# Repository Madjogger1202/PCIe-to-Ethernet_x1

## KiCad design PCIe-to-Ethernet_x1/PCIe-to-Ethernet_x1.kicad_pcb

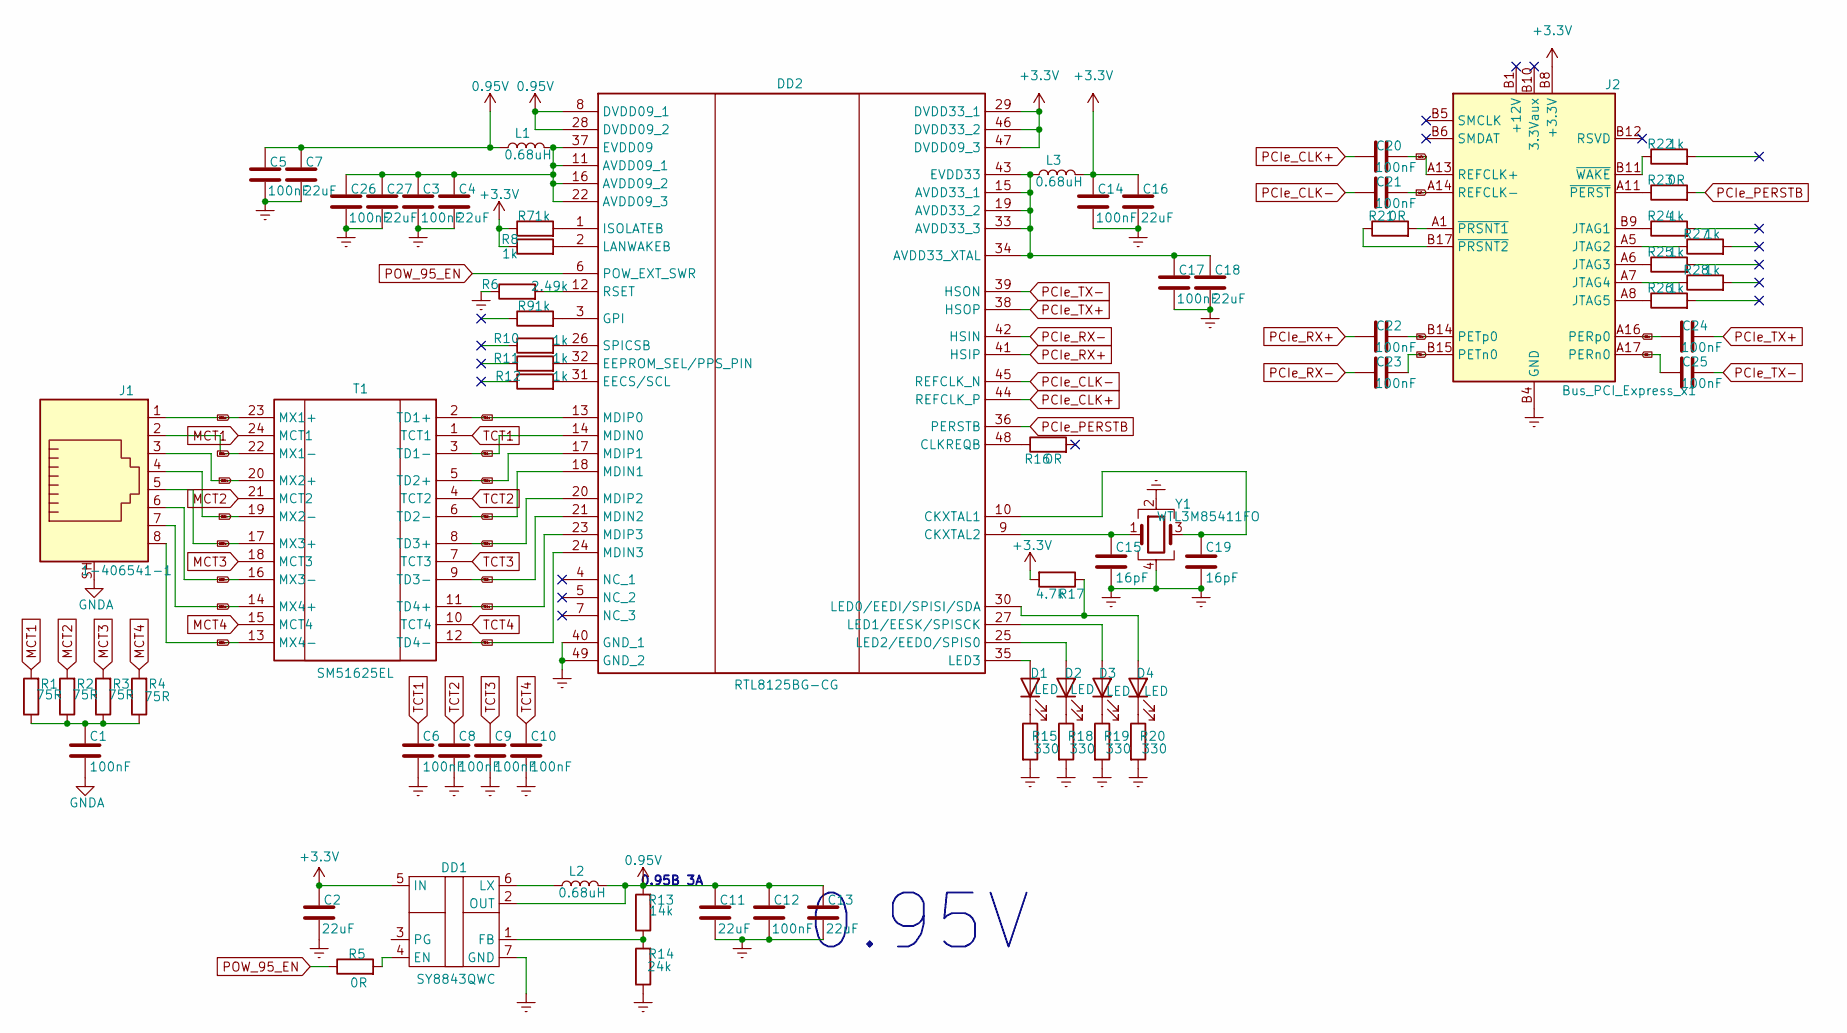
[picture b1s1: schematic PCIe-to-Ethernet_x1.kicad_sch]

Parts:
C1, C3, C5, C6, C8, C9, C10, C12, C14, C17, C20, C21, C22, C23, C24, C25, C26: 100nF; C_0402_1005Metric
C2, C4, C7, C11, C13, C16, C18, C27: 22uF; C_0402_1005Metric
C15, C19: 16pF; C_0402_1005Metric
D1, D2, D3, D4: LED; LED_0402_1005Metric
DD1: SY8843QWC
DD2: RTL8125BG-CG; QFN40P600X600X100-49N; Manufacturer_Part_Number RTL8125BG-CG
J1: 1-406541-1; RJ45_Amphenol_RJHSE5380
J2: Bus_PCI_Express_x1; BUS_PCIexpress_x1
L1, L2, L3: 0.68uH; L_Cenker_CKCS4020
R1, R2, R3, R4: 75R; R_0402_1005Metric
R5, R16, R21, R23: 0R; R_0402_1005Metric
R6: 2.49k; R_0402_1005Metric
R7, R8, R9, R10, R11, R12, R22, R24, R25, R26, R27, R28: 1k; R_0402_1005Metric
R13: 14k; R_0402_1005Metric
R14: 24k; R_0402_1005Metric
R15, R18, R19, R20: 330; R_0402_1005Metric
R17: 4.7k; R_0402_1005Metric
T1: SM51625EL; SOIC127P1600X625-24N; Manufacturer_Part_Number SM51625EL; Mouser Part Number 652-SM51625EL
Y1: WTL3M85411FO; Crystal_SMD_3225-4Pin_3.2x2.5mm

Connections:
0.95V: C5.1, C7.1, C11.1, C12.1, C13.1, DD1.2 (OUT), DD2.8 (DVDD09_1), DD2.28 (DVDD09_2), L1.1, L2.2, R13.2
+3.3V: C2.1, C14.1, C16.1, DD1.5 (IN), DD2.29 (DVDD33_1), DD2.46 (DVDD33_2), DD2.47 (DVDD09_3), J2.A9 (+3.3V), J2.A10 (+3.3V), J2.B8 (+3.3V), L3.2, R7.1, R8.1, R17.2
Earth: C2.2, C3.2, C4.2, C5.2, C6.2, C7.2, C8.2, C9.2, C10.2, C11.2, C12.2, C13.2, C14.2, C15.2, C16.2, C17.2, C18.2, C19.2, C26.2, C27.2, DD1.7 (GND), DD2.40 (GND_1), DD2.49 (GND_2), J2.A4 (GND), J2.A12 (GND), J2.A15 (GND), J2.A18 (GND), J2.B4 (GND), J2.B7 (GND), J2.B13 (GND), J2.B16 (GND), J2.B18 (GND), R6.1, R14.1, R15.2, R18.2, R19.2, R20.2, Y1.2, Y1.4
GNDA: C1.2, J1.SH
MCT1: R1.2, T1.24 (MCT1)
MCT2: R2.2, T1.21 (MCT2)
MCT3: R3.2, T1.18 (MCT3)
MCT4: R4.2, T1.15 (MCT4)
MX1+: J1.1, T1.23 (MX1+)
MX1-: J1.2, T1.22 (MX1-)
MX2+: J1.3, T1.20 (MX2+)
MX2-: J1.4, T1.19 (MX2-)
MX3+: J1.5, T1.17 (MX3+)
MX3-: J1.6, T1.16 (MX3-)
MX4+: J1.7, T1.14 (MX4+)
MX4-: J1.8, T1.13 (MX4-)
unnamed: C1.1, R1.1, R2.1, R3.1, R4.1
unnamed: D1.2 (A), DD2.35 (LED3)
unnamed: D1.1 (K), R15.1
unnamed: D2.2 (A), DD2.25 (LED2/EEDO/SPIS0)
unnamed: D2.1 (K), R18.1
unnamed: D3.2 (A), DD2.27 (LED1/EESK/SPISCK)
unnamed: D3.1 (K), R19.1
unnamed: D4.2 (A), DD2.30 (LED0/EEDI/SPISI/SDA), R17.1
unnamed: D4.1 (K), R20.1
unnamed: DD1.4 (EN), R5.2
unnamed: DD1.1 (FB), R13.1, R14.2
unnamed: DD1.6 (LX), L2.1
unnamed: C3.1, C4.1, C26.1, C27.1, DD2.11 (AVDD09_1), DD2.16 (AVDD09_2), DD2.22 (AVDD09_3), DD2.37 (EVDD09), L1.2
unnamed: C17.1, C18.1, DD2.15 (AVDD33_1), DD2.19 (AVDD33_2), DD2.33 (AVDD33_3), DD2.34 (AVDD33_XTAL), DD2.43 (EVDD33), L3.1
unnamed: C19.1, DD2.10 (CKXTAL1), Y1.3
unnamed: C15.1, DD2.9 (CKXTAL2), Y1.1
unnamed: DD2.48 (CLKREQB), R16.1
unnamed: DD2.31 (EECS/SCL), R12.2
unnamed: DD2.32 (EEPROM_SEL/PPS_PIN), R11.2
unnamed: DD2.3 (GPI), R9.2
unnamed: DD2.1 (ISOLATEB), R7.2
unnamed: DD2.2 (LANWAKEB), R8.2
unnamed: DD2.12 (RSET), R6.2
unnamed: DD2.26 (SPICSB), R10.2
unnamed: J2.B9 (JTAG1), R24.1
unnamed: J2.A5 (JTAG2), R27.1
unnamed: J2.A6 (JTAG3), R25.1
unnamed: J2.A7 (JTAG4), R28.1
unnamed: J2.A8 (JTAG5), R26.1
unnamed: J2.A11 (~PERST), R23.1
unnamed: J2.A1 (~PRSNT1), R21.2
unnamed: J2.B17 (~PRSNT2), R21.1
unnamed: J2.B11 (~WAKE), R22.1
PCIe_CLK+: C20.1, DD2.44 (REFCLK_P)
PCIe_CLK-: C21.1, DD2.45 (REFCLK_N)
PCIe_PERSTB: DD2.36 (PERSTB), R23.2
PCIe_RX+: C22.1, DD2.41 (HSIP)
PCIe_RX-: C23.1, DD2.42 (HSIN)
PCIe_TX+: C24.2, DD2.38 (HSOP)
PCIe_TX-: C25.2, DD2.39 (HSON)
POW_95_EN: DD2.6 (POW_EXT_SWR), R5.1
RX+: C24.1, J2.A16 (PERp0)
RX-: C25.1, J2.A17 (PERn0)
TCT1: C6.1, T1.1 (TCT1)
TCT2: C8.1, T1.4 (TCT2)
TCT3: C9.1, T1.7 (TCT3)
TCT4: C10.1, T1.10 (TCT4)
TD1+: DD2.13 (MDIP0), T1.2 (TD1+)
TD1-: DD2.14 (MDIN0), T1.3 (TD1-)
TD2+: DD2.17 (MDIP1), T1.5 (TD2+)
TD2-: DD2.18 (MDIN1), T1.6 (TD2-)
TD3+: DD2.20 (MDIP2), T1.8 (TD3+)
TD3-: DD2.21 (MDIN2), T1.9 (TD3-)
TD4+: DD2.23 (MDIP3), T1.11 (TD4+)
TD4-: DD2.24 (MDIN3), T1.12 (TD4-)
TX+: C22.2, J2.B14 (PETp0)
TX-: C23.2, J2.B15 (PETn0)
ref+: C20.2, J2.A13 (REFCLK+)
ref-: C21.2, J2.A14 (REFCLK-)

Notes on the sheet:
0.95В 3А
0.95V

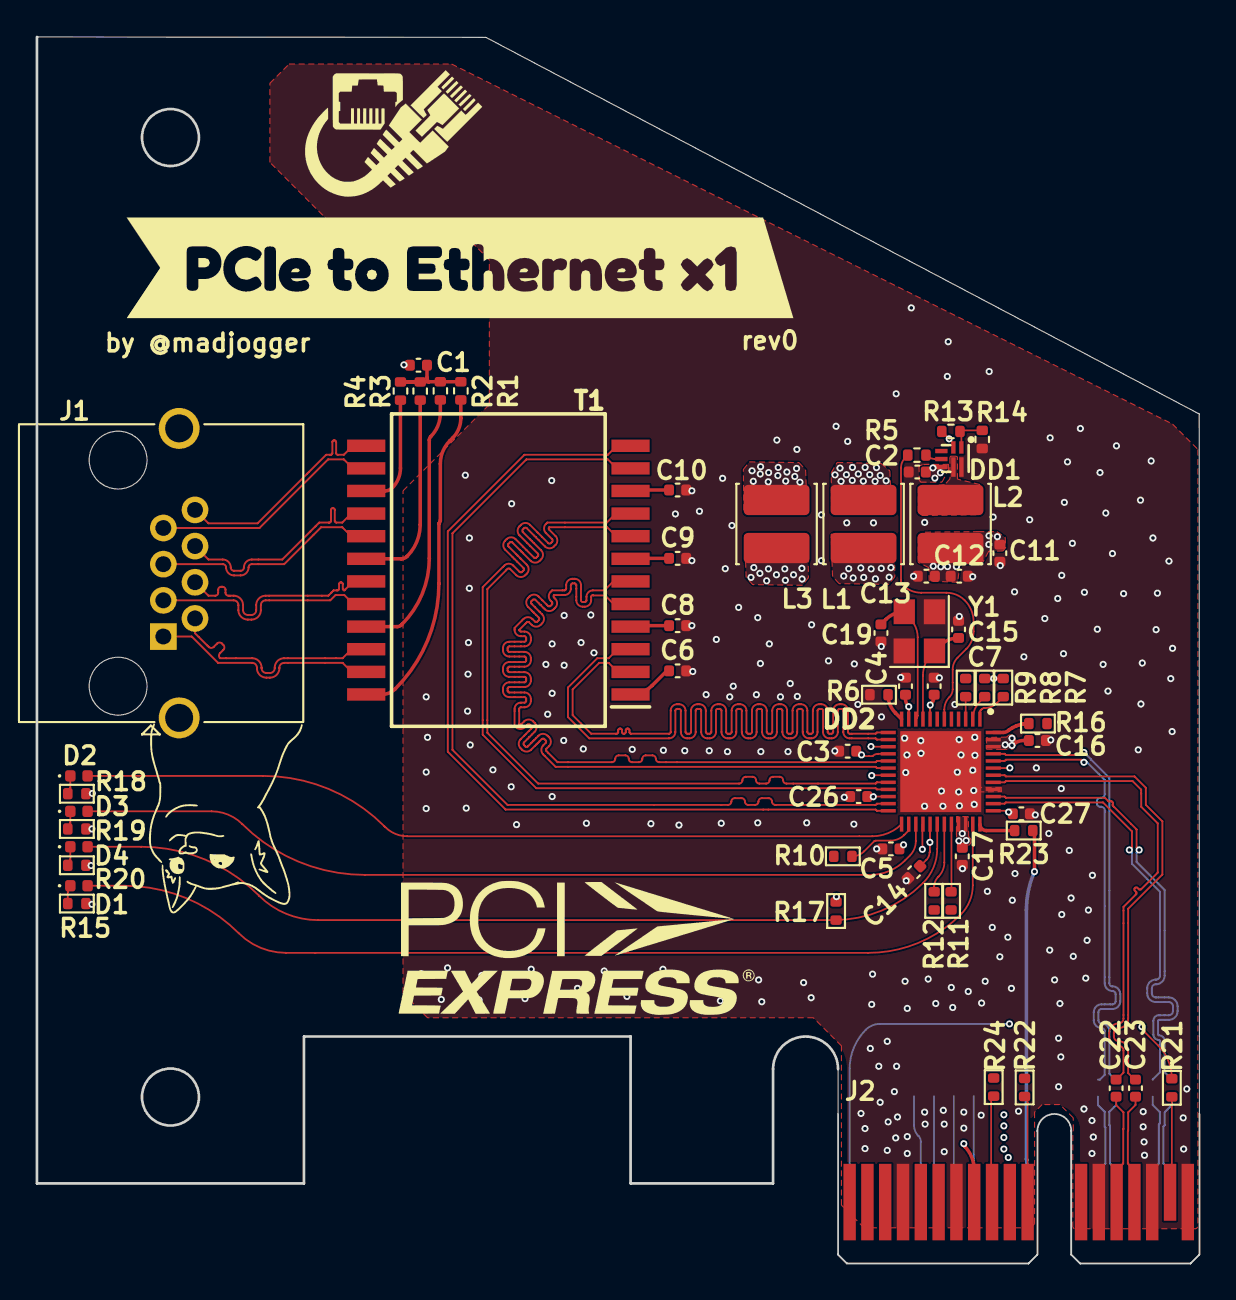
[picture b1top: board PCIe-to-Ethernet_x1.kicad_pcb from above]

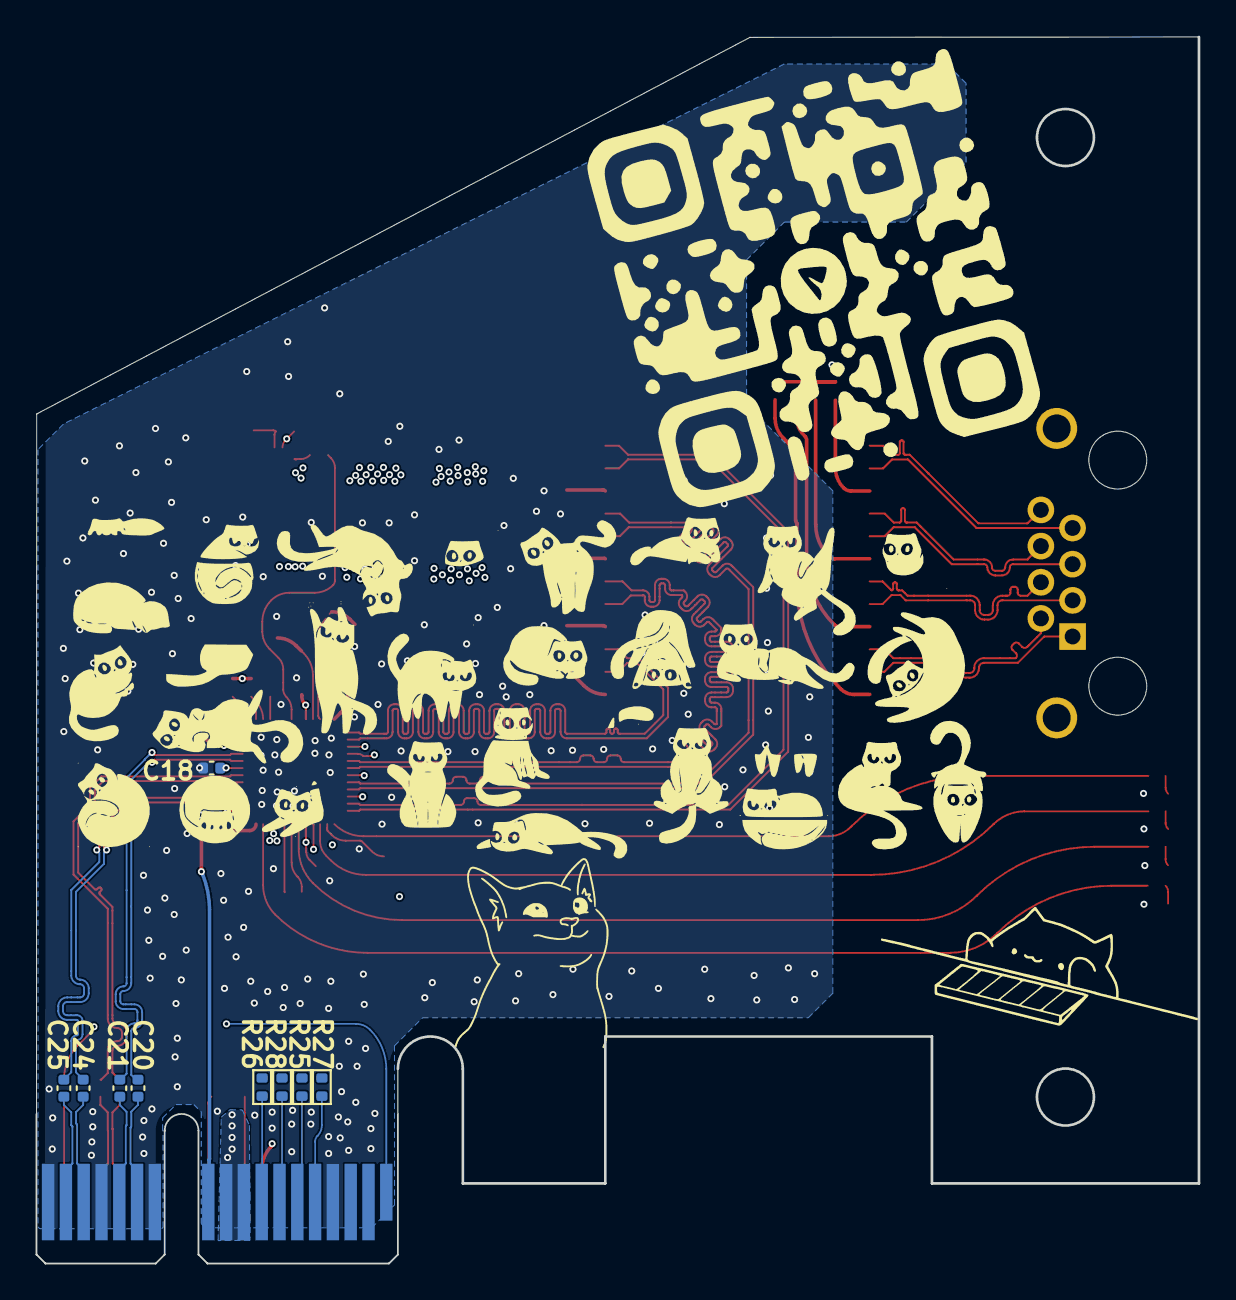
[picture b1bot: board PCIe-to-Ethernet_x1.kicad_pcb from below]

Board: 4 copper layers, 65.3 x 68.9 mm, 70 parts (9 on the bottom side), 75 nets.

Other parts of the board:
J1#2: PCIexpress_bracket; PCIexpress_bracket_low
kibuzzard-67DEDE50: G***; kibuzzard-67DEDE50

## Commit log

2025-03-22 rev0 готова
2025-03-22 Чуть поправил землю чтобы можно было подпилить разъём PCIe ( для лучшего контакта )
2025-03-23 Исправил отсутствие перекрёстного соединения на PCIe
